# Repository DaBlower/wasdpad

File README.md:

# obob's wasdpad
This is my submission to hackpad (v5?)
It has 6 switches, rgb, an OLED display and 3 different layers, WASD mode, arrow key mode and media (changing layers and volume eg)

## Features
* 8 Neopixels
* A 0.91 inch OLED screen
* 6 Cherry MX Switches
* KMK firmware with layers and support for neopixels and the oled

# PCB
Here a some pictures of my PCB
| **Schematic** | **PCB** |
|---------------|---------|
|||

# CAD
I designed the case in Fusion 360 and added a duck (that you can barely see in the render)

||

# BOM
* 1 Seeed XIAO RP2040
* 6 THT 1N4148 Diodes
* 6 MX-style switches
* 1 0.91 inch OLED display
* 6 Keycaps
* 8 SK6812 MINI-E LEDs
* 4 M3x16mm screws
* 4 M3x5mx4mm heatset inserts
* 1 3D printed case (find the CAD files in /case)

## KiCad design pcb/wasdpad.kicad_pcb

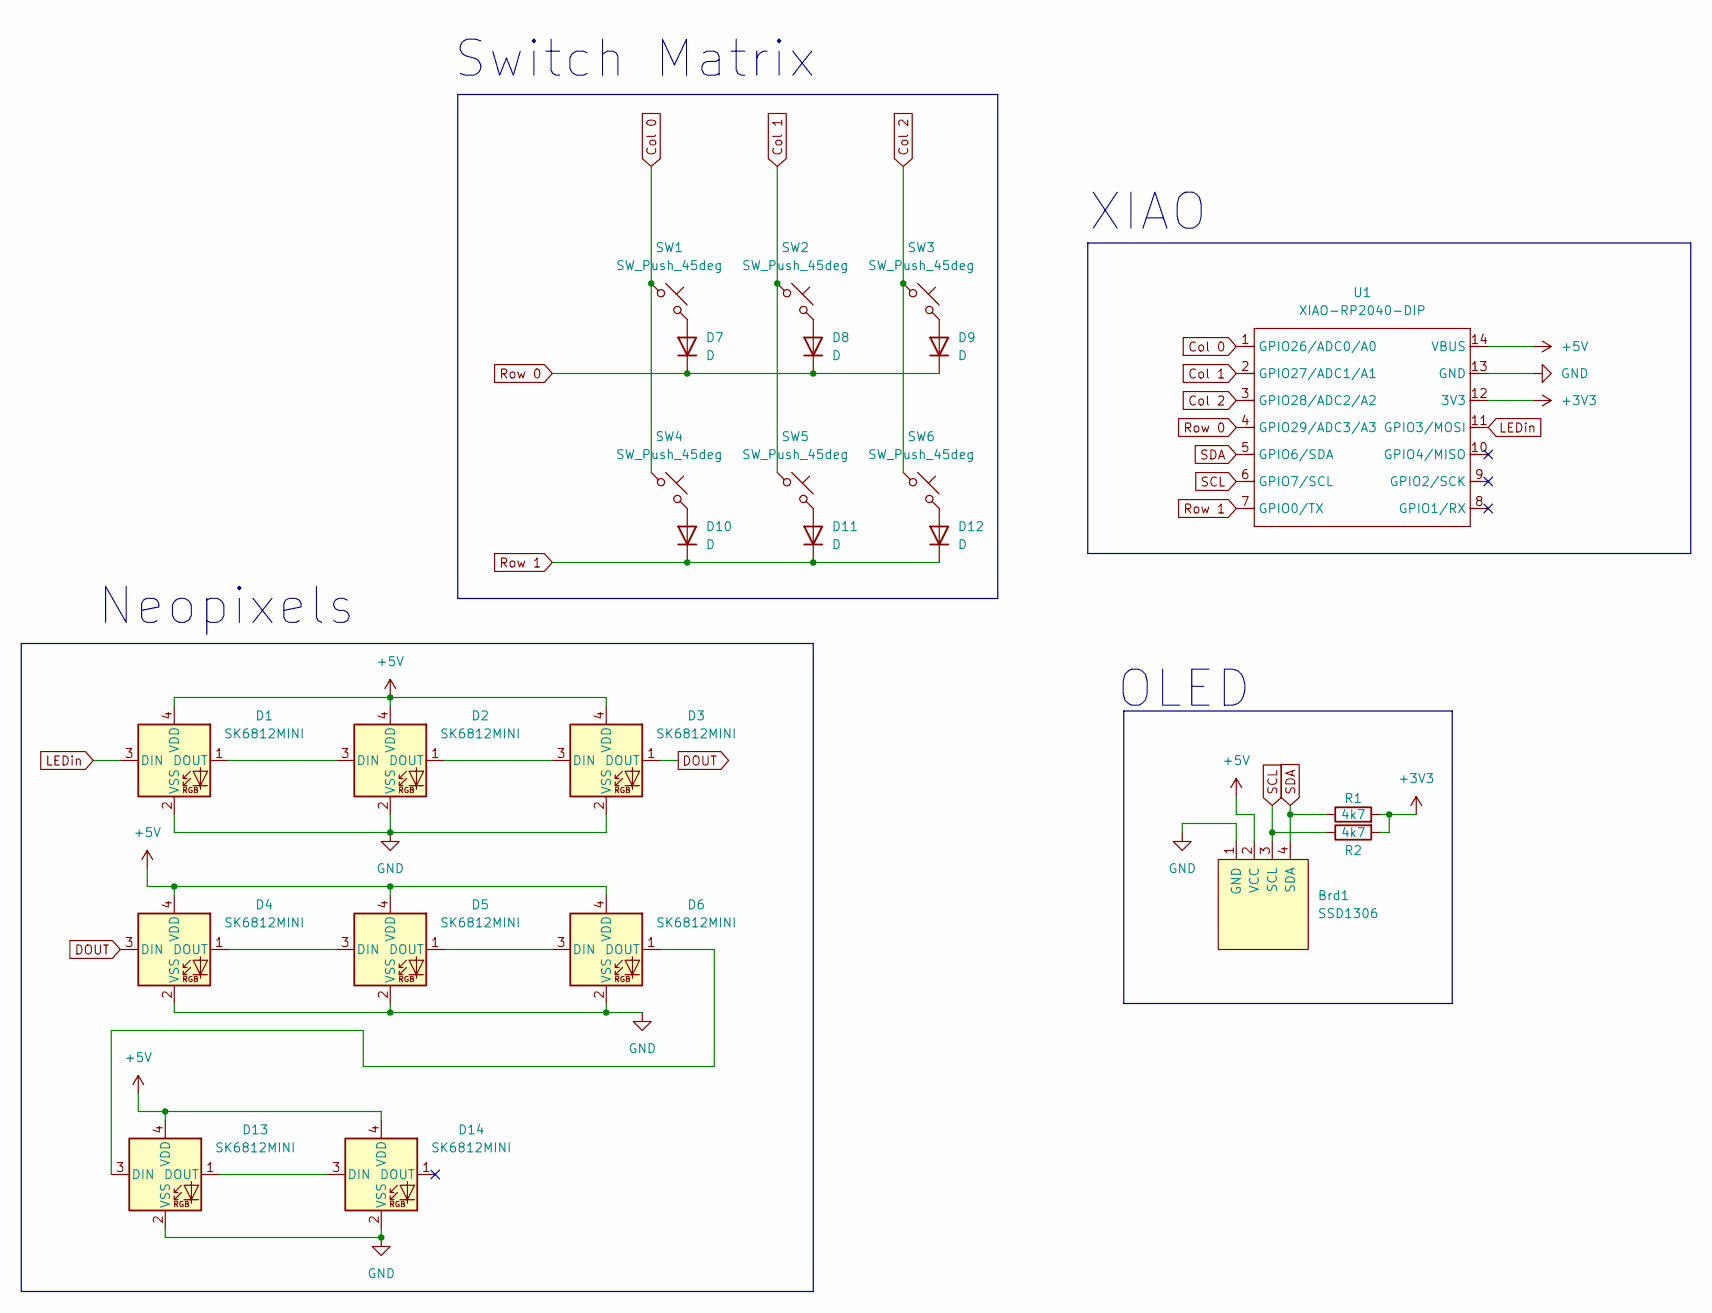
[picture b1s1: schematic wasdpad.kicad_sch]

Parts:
Brd1: SSD1306; SSD1306-0.91-OLED-4pin-128x32
D1, D2, D3, D4, D5, D6, D13, D14: SK6812MINI; SK6812MINI-E
D7, D8, D9, D10, D11, D12: D; D_DO-35_SOD27_P7.62mm_Horizontal
R1, R2: 4k7; R_Axial_DIN0204_L3.6mm_D1.6mm_P7.62mm_Horizontal
SW1, SW2, SW3, SW4, SW5, SW6: SW_Push_45deg; MX-Solderable-1U
U1: XIAO-RP2040-DIP

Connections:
+3V3: R1.2, R2.2, U1.12 (3V3)
+5V: Brd1.2 (VCC), D1.4 (VDD), D2.4 (VDD), D3.4 (VDD), D4.4 (VDD), D5.4 (VDD), D6.4 (VDD), D13.4 (VDD), D14.4 (VDD), U1.14 (VBUS)
Col 0: SW1.1, SW4.1, U1.1 (GPIO26/ADC0/A0)
Col 1: SW2.1, SW5.1, U1.2 (GPIO27/ADC1/A1)
Col 2: SW3.1, SW6.1, U1.3 (GPIO28/ADC2/A2)
DOUT: D3.1 (DOUT), D4.3 (DIN)
GND: Brd1.1 (GND), D1.2 (VSS), D2.2 (VSS), D3.2 (VSS), D4.2 (VSS), D5.2 (VSS), D6.2 (VSS), D13.2 (VSS), D14.2 (VSS), U1.13 (GND)
LEDin: D1.3 (DIN), U1.11 (GPIO3/MOSI)
unnamed: D1.1 (DOUT), D2.3 (DIN)
unnamed: D2.1 (DOUT), D3.3 (DIN)
unnamed: D4.1 (DOUT), D5.3 (DIN)
unnamed: D5.1 (DOUT), D6.3 (DIN)
unnamed: D7.2 (A), SW1.2
unnamed: D8.2 (A), SW2.2
unnamed: D9.2 (A), SW3.2
unnamed: D10.2 (A), SW4.2
unnamed: D11.2 (A), SW5.2
unnamed: D12.2 (A), SW6.2
unnamed: D6.1 (DOUT), D13.3 (DIN)
unnamed: D13.1 (DOUT), D14.3 (DIN)
Row 0: D7.1 (K), D8.1 (K), D9.1 (K), U1.4 (GPIO29/ADC3/A3)
Row 1: D10.1 (K), D11.1 (K), D12.1 (K), U1.7 (GPIO0/TX)
SCL: Brd1.3 (SCL), R2.1, U1.6 (GPIO7/SCL)
SDA: Brd1.4 (SDA), R1.1, U1.5 (GPIO6/SDA)

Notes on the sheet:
OLED
Neopixels
Switch Matrix
XIAO

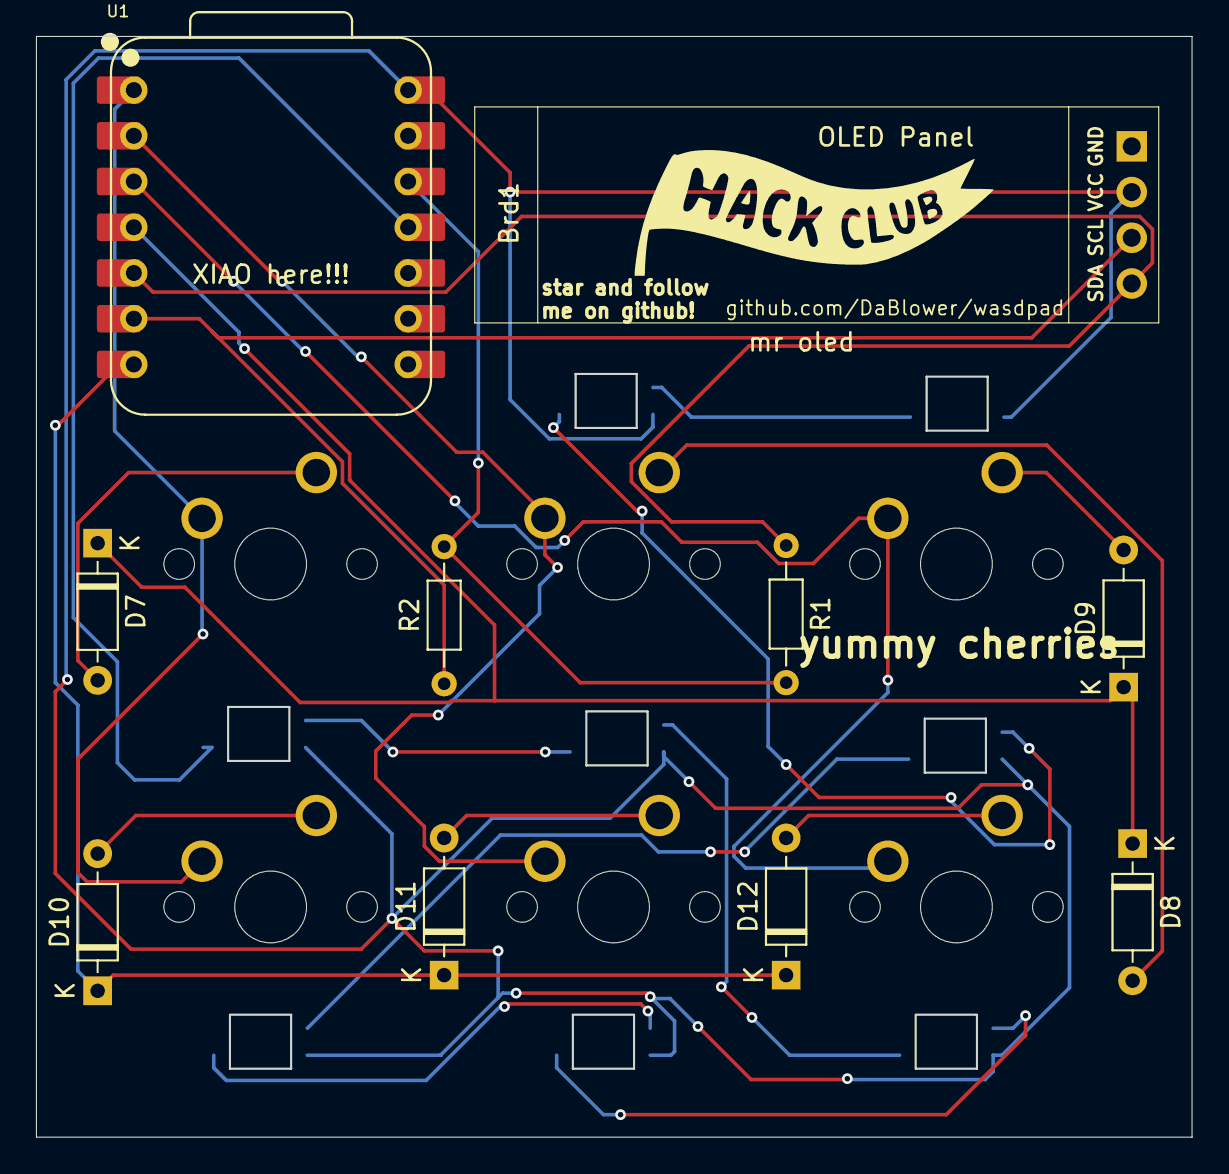
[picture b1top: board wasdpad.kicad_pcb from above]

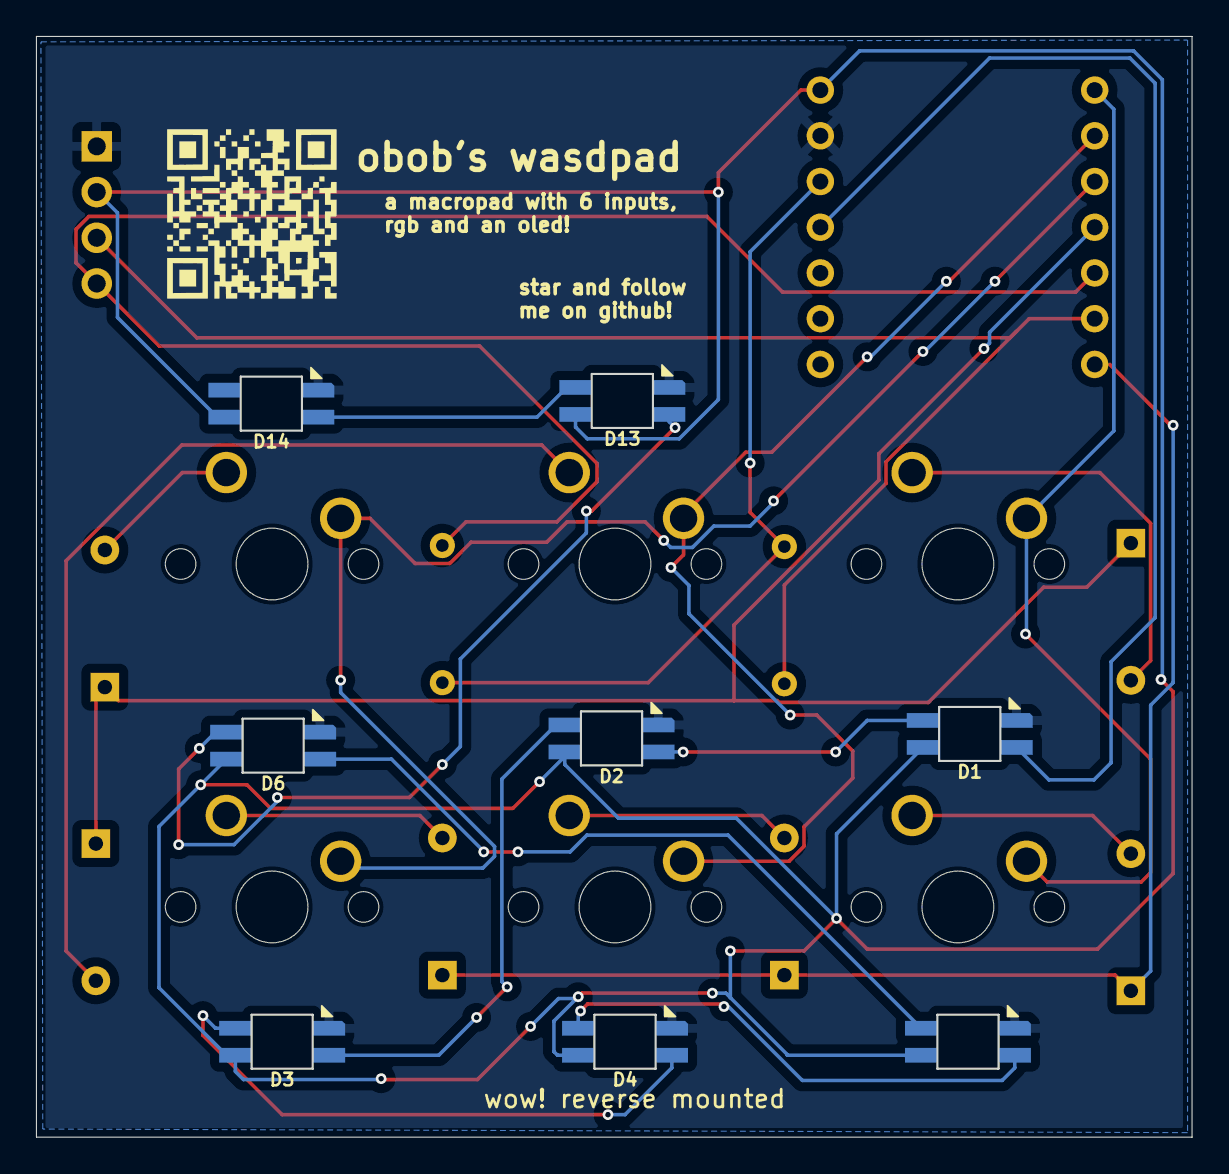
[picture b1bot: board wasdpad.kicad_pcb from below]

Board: 2 copper layers, 64.1 x 61.1 mm, 24 parts (8 on the bottom side), 24 nets.

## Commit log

2025-11-14 kicad init
2025-11-14 add xiao symbols
2025-11-14 oops forgot to add symbols to settings
2025-11-15 finished schema
2025-11-15 pcb layout
2025-11-15 fix layout + 3d models for mx
2025-11-15 extra neopixels
2025-11-15 add remaining 3d models
2025-11-15 fix drc issues
2025-11-15 step export of pcb
2025-11-15 reformat folder structure and add case
2025-11-15 update top plate
2025-11-15 fix unconnected neopixel
2025-11-15 add firmware
2025-11-15 add readme
2025-11-15 add production files
2025-11-19 update production
2025-11-19 fix silkscreen
2025-11-20 final cad files
2025-11-20 add final stls
